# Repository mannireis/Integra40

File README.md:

# Integra40
A keyboard that is split reversible 40%ish and has an integratted mcu

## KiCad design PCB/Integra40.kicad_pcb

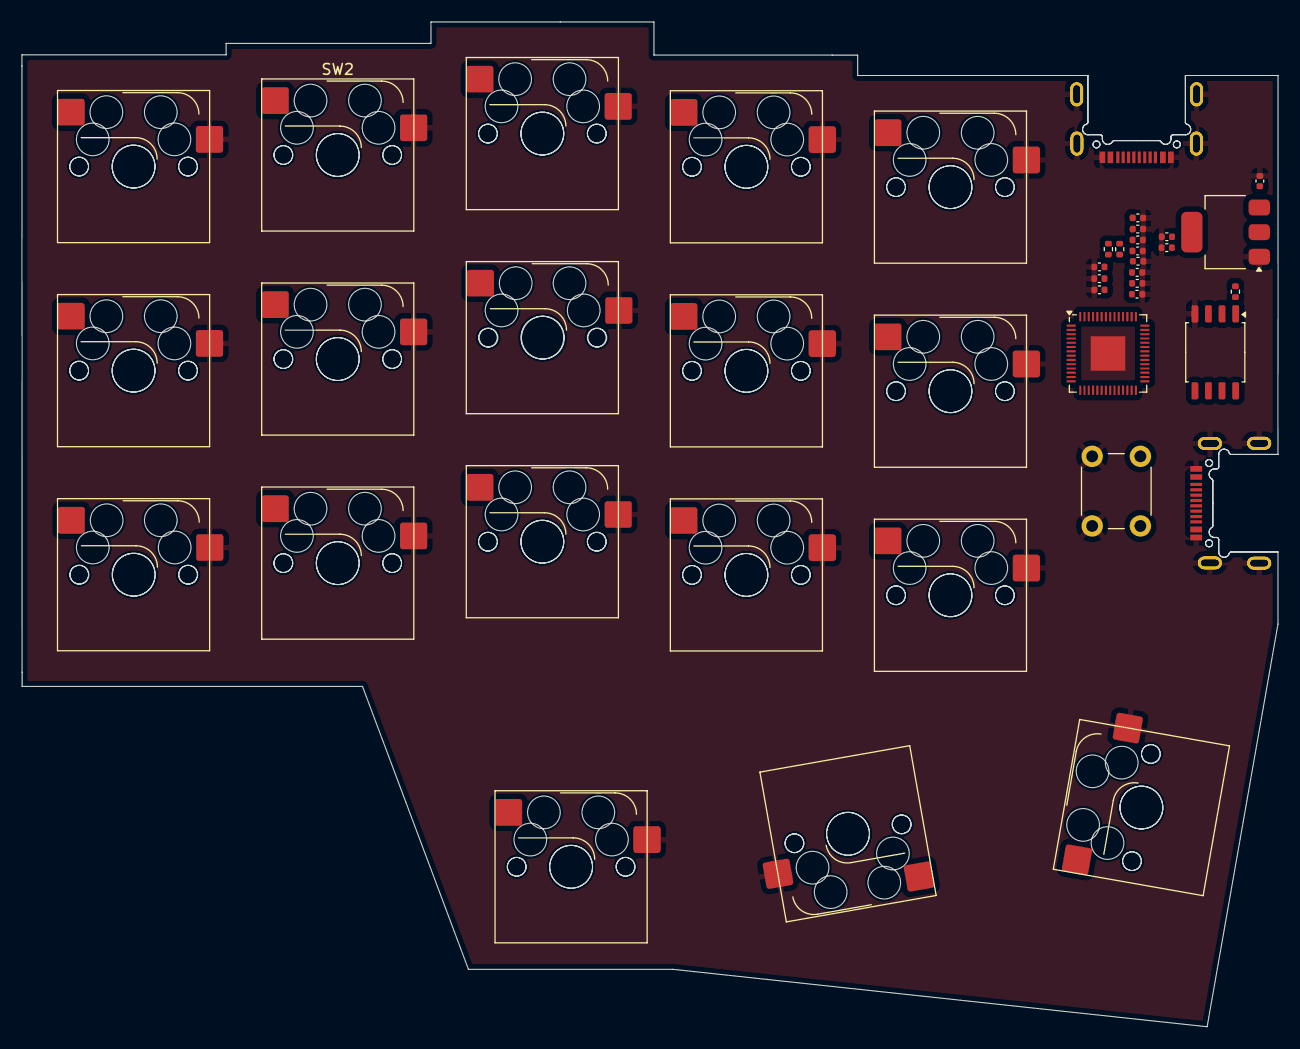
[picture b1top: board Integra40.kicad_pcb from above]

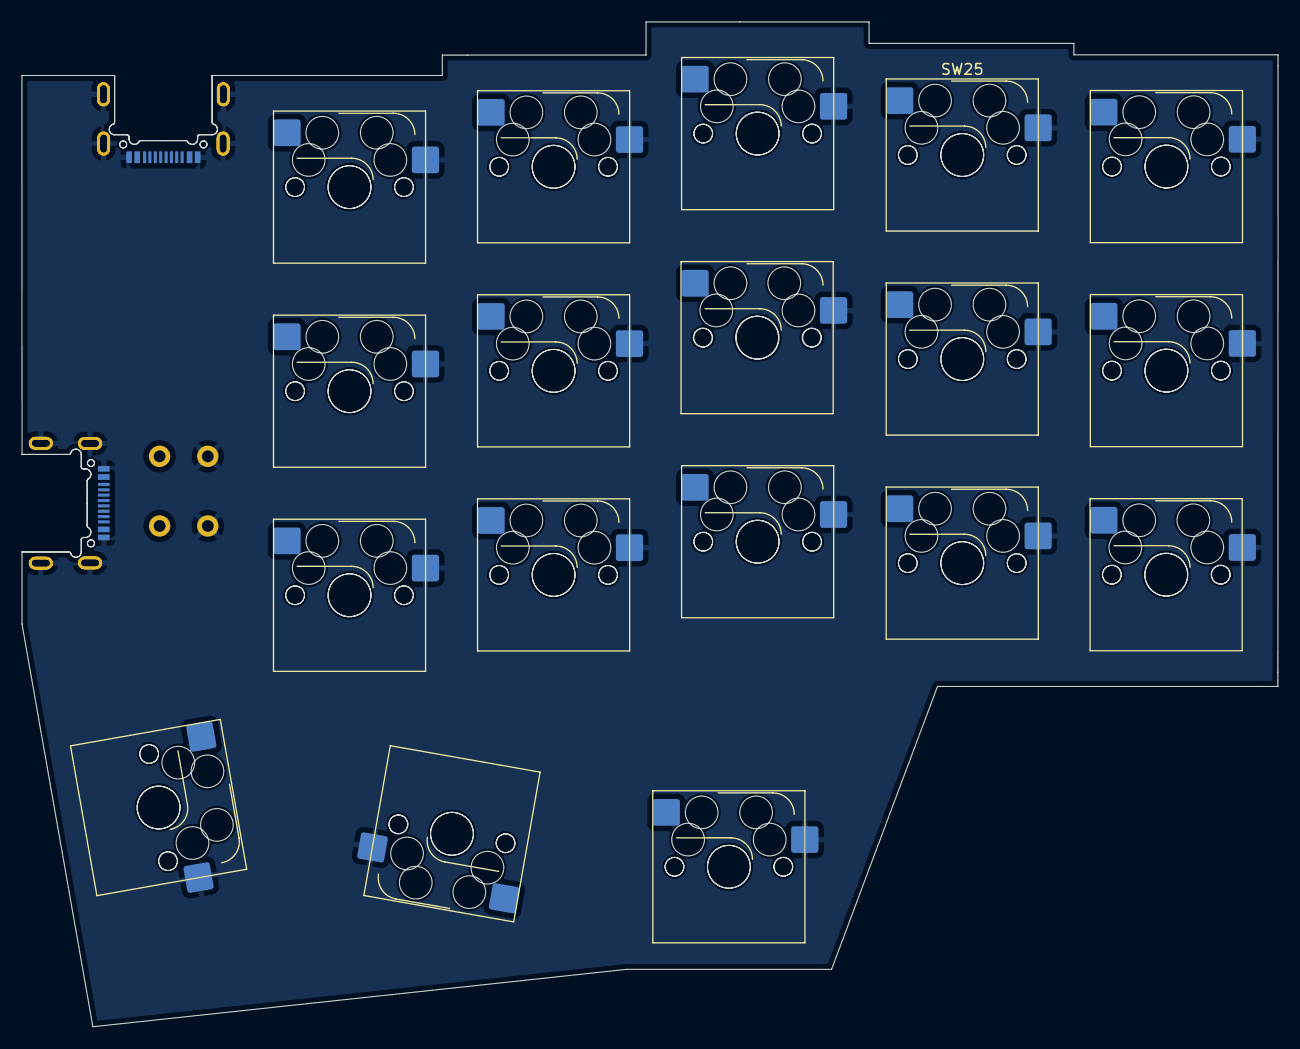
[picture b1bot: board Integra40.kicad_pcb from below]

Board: 2 copper layers, 117.3 x 93.8 mm, 61 parts (20 on the bottom side), 35 nets, no tracks yet.

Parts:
C1, C2: 10u; C_0402_1005Metric
C3, C6: 1u; C_0402_1005Metric
C4, C5, C7, C8, C9, C10, C11, C12, C13, C14: 100n; C_0402_1005Metric
J1, J2, J3, J4: USB_C_Receptacle_USB2.0_16P; USB_C_HRO_TYPE-C-31-M-14
R1, R2: 27.4; R_0402_1005Metric
R3: 1k; R_0402_1005Metric
SW1, SW2, SW3, SW4, SW5, SW6, SW7, SW8, SW9, SW10, SW11, SW12, SW13, SW14, SW15, SW16, SW21, SW22, SW23, SW24, SW25, SW26, SW27, SW29, SW30, SW31, SW33, SW34, SW35, SW37, SW38, SW39: SW_Push_45deg; Hotswap_MX_1.00u
SW17, SW28: SW_Push_45deg; Hotswap_MX_1.50u
SW18, SW32: SW_Push_45deg; Hotswap_MX_2.00u
SW41: SW_Push; SW_PUSH_6mm_H4.3mm
U1: RP2040; QFN-56-1EP_7x7mm_P0.4mm_EP3.2x3.2mm
U2: NCP1117-3.3_SOT223; SOT-223-3_TabPin2
U3: W25Q32JVSS; SOIC-8_5.3x5.3mm_P1.27mm

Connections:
+1V1: C3.1, C4.1, C5.1, U1.23 (DVDD), U1.45 (VREG_VOUT), U1.50 (DVDD)
+3V3: C2.1, C6.1, C7.1, C8.1, C9.1, C10.1, C11.1, C12.1, C13.1, C14.1, U1.1 (IOVDD), U1.10 (IOVDD), U1.22 (IOVDD), U1.33 (IOVDD), U1.42 (IOVDD), U1.43 (ADC_AVDD), U1.44 (VREG_IN), U1.48 (USB_VDD), U1.49 (IOVDD), U2.2 (VO), U3.8 (VCC)
/CLK: U1.52 (QSPI_SCLK), U3.6 (CLK)
/GPIO00: SW1.2, SW21.2, U1.2 (GPIO0)
/GPIO01: SW2.2, SW25.2, U1.3 (GPIO1)
/GPIO02: SW3.2, SW29.2, U1.4 (GPIO2)
/GPIO03: SW4.2, SW33.2, U1.5 (GPIO3)
/GPIO04: SW5.2, SW37.2, U1.6 (GPIO4)
/GPIO05: SW6.2, SW22.2, U1.7 (GPIO5)
/GPIO06: SW7.2, SW26.2, U1.8 (GPIO6)
/GPIO07: SW8.2, SW30.2, U1.9 (GPIO7)
/GPIO08: SW9.2, SW34.2, U1.11 (GPIO8)
/GPIO09: SW10.2, SW38.2, U1.12 (GPIO9)
/GPIO10: SW11.2, SW23.2, U1.13 (GPIO10)
/GPIO11: SW12.2, SW27.2, U1.14 (GPIO11)
/GPIO12: SW13.2, SW31.2, U1.15 (GPIO12)
/GPIO13: SW14.2, SW35.2, U1.16 (GPIO13)
/GPIO14: SW15.2, SW39.2, U1.17 (GPIO14)
/GPIO15: SW16.2, SW24.2, U1.18 (GPIO15)
/GPIO16: SW17.2, SW28.2, U1.27 (GPIO16)
/GPIO17: SW18.2, SW32.2, U1.28 (GPIO17), U1.30 (GPIO19)
/RX: J3.A7 (D-), J3.B7 (D-), J4.A7 (D-), J4.B7 (D-), U1.41 (GPIO29_ADC3)
/SD0: U1.53 (QSPI_SD0), U3.5 (DI/IO_{0})
/SD1: U1.55 (QSPI_SD1), U3.2 (DO/IO_{1})
/SD2: U1.54 (QSPI_SD2), U3.3 (~WP/IO_{2})
/SD3: U1.51 (QSPI_SD3), U3.7 (~HOLD/~RESET/IO_{3})
/SS: R3.2, U1.56 (QSPI_SS), U3.1 (~CS)
/TX: J3.A6 (D+), J3.B6 (D+), J4.A6 (D+), J4.B6 (D+), U1.40 (GPIO28_ADC2)
/USB-DM: J1.A7 (D-), J1.B7 (D-), J2.A7 (D-), J2.B7 (D-), R2.1
/USB-DP: J1.A6 (D+), J1.B6 (D+), J2.A6 (D+), J2.B6 (D+), R1.1
GND: C1.2, C2.2, C3.2, C4.2, C5.2, C6.2, C7.2, C8.2, C9.2, C10.2, C11.2, C12.2, C13.2, C14.2, J1.A1 (GND), J1.A12 (GND), J1.B1 (GND), J1.B12 (GND), J1.S1 (SHIELD), J2.A1 (GND), J2.A12 (GND), J2.B1 (GND), J2.B12 (GND), J2.S1 (SHIELD), J3.A1 (GND), J3.A12 (GND), J3.B1 (GND), J3.B12 (GND), J3.S1 (SHIELD), J4.A1 (GND), J4.A12 (GND), J4.B1 (GND), J4.B12 (GND), J4.S1 (SHIELD), SW1.1, SW2.1, SW3.1, SW4.1, SW5.1, SW6.1, SW7.1, SW8.1, SW9.1, SW10.1, SW11.1, SW12.1, SW13.1, SW14.1, SW15.1, SW16.1, SW17.1, SW18.1, SW21.1, SW22.1, SW23.1, SW24.1, SW25.1, SW26.1, SW27.1, SW28.1, SW29.1, SW30.1, SW31.1, SW32.1, SW33.1, SW34.1, SW35.1, SW37.1, SW38.1, SW39.1, SW41.1, U1.19 (TESTEN), U1.57 (GND), U2.1 (GND), U3.4 (GND)
unnamed: R3.1, SW41.2
unnamed: R2.2, U1.46 (USB_DM)
unnamed: R1.2, U1.47 (USB_DP)
VBUS: C1.1, J1.A4 (VBUS), J1.A9 (VBUS), J1.B4 (VBUS), J1.B9 (VBUS), J2.A4 (VBUS), J2.A9 (VBUS), J2.B4 (VBUS), J2.B9 (VBUS), J3.A4 (VBUS), J3.A9 (VBUS), J3.B4 (VBUS), J3.B9 (VBUS), J4.A4 (VBUS), J4.A9 (VBUS), J4.B4 (VBUS), J4.B9 (VBUS), U2.3 (VI)

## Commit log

2025-06-04 Rename journal.md to JOURNAL.md
2025-06-04 Add PCB
